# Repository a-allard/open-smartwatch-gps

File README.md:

# Open-Smartwatch KiCAD files

Repo for kicad schematic, board and gerber files. This project is in development and is not ready for release.

If all you want to know is how to build skip down to [Build Info](##Build Info)

#### Forking to move forward

The [original project ](https://github.com/Open-Smartwatch/open-smartwatch-gps) seems to have lost some momentum on development.  There is an [issue here](https://github.com/Open-Smartwatch/open-smartwatch-gps/issues/10) to discuss merging these changes into the original project.  One of the goals of this fork and update is to minimize any serious changes to [the os](https://github.com/Open-Smartwatch/open-smartwatch-os).  If all goes well, the OS should be able to be dropped on here with little to no modifications.  (that is the goal time will tell for sure.)

Right now this is a 2 layer design.  If this works it will greatly reduce the overall cost.  Have to see how this performs.

## Tools

To view/modify the files from this repository install [KiCAD](https://kicad.org).  You'll need version 7.0 or higher.  This will be bumped in Janurary of 2024 to KiCad 8.0.

All footprints, schematic symbols and 3d models should be self contained winthin the project.  This means you should be able to open the kicad project anywhere with or without the default kicad libraries and play with things without worry about missing pieces.

## Schematic
Updated as of 10/20/2023.  May change but if it does it should be minor changes.

Update on 1/7/2024.... Happy New Year to all!  Been quite for awhile as getting boards built and tested took quite a while.  Found a few issues.  Working on fixing them before another spin.  Probably be respinning sometime around May...?

## Plots

## Build Info

To get some raw PCBs the best way would be [pcbway](https://pcbway.com).  Once this project has been built and tested the design will be published on pcbway for anyone to order with a couple clicks.

Next you'll have to either build this yourself or get these fabricated.  If you want to get the boards fabricated pcbway does a decent job.  You'll have to export the position files and put the BOM in pcbway format.

If you choose to solder these youself the smallest components are 0402 and QFNs.  Not the most friendly but can be done with a decent soldering iron.

### BOM

NOTE: **This is a preliminary BOM**  After testing this could change some.

[HTML BOM](https://github.com/a-allard/open-smartwatch-gps/blob/master/bom/OSW_GPS_Rev-4.0.html)  (best to download for a pretty view)

For actual parts you'll need
* [Digi-Key cart](https://www.digikey.com/short/5wz73v93) with most everything needed for a build of 1.
* [Display](https://www.buydisplay.com/1-28-inch-tft-lcd-display-240x240-round-circle-screen-for-smart-watch)
* A LiPo battery (Has not yet been selected but you should be able to power this from USB for initial debugging.  Any generic lipo should work just make sure the pinout works with the connector)

Total cost from DK ~$55.  The display is ~$15 including shipping.  With a battery this should bring the total BOM cost per watch to about ~$110 including boards from pcbway.com.  Note this is for a single watch but you'll have to order 5 boards from pcbway.com

Don't forget to get some decent fine solder while or solder paste as you will need it!

If you like this project, please consider supporting my open source projects through:

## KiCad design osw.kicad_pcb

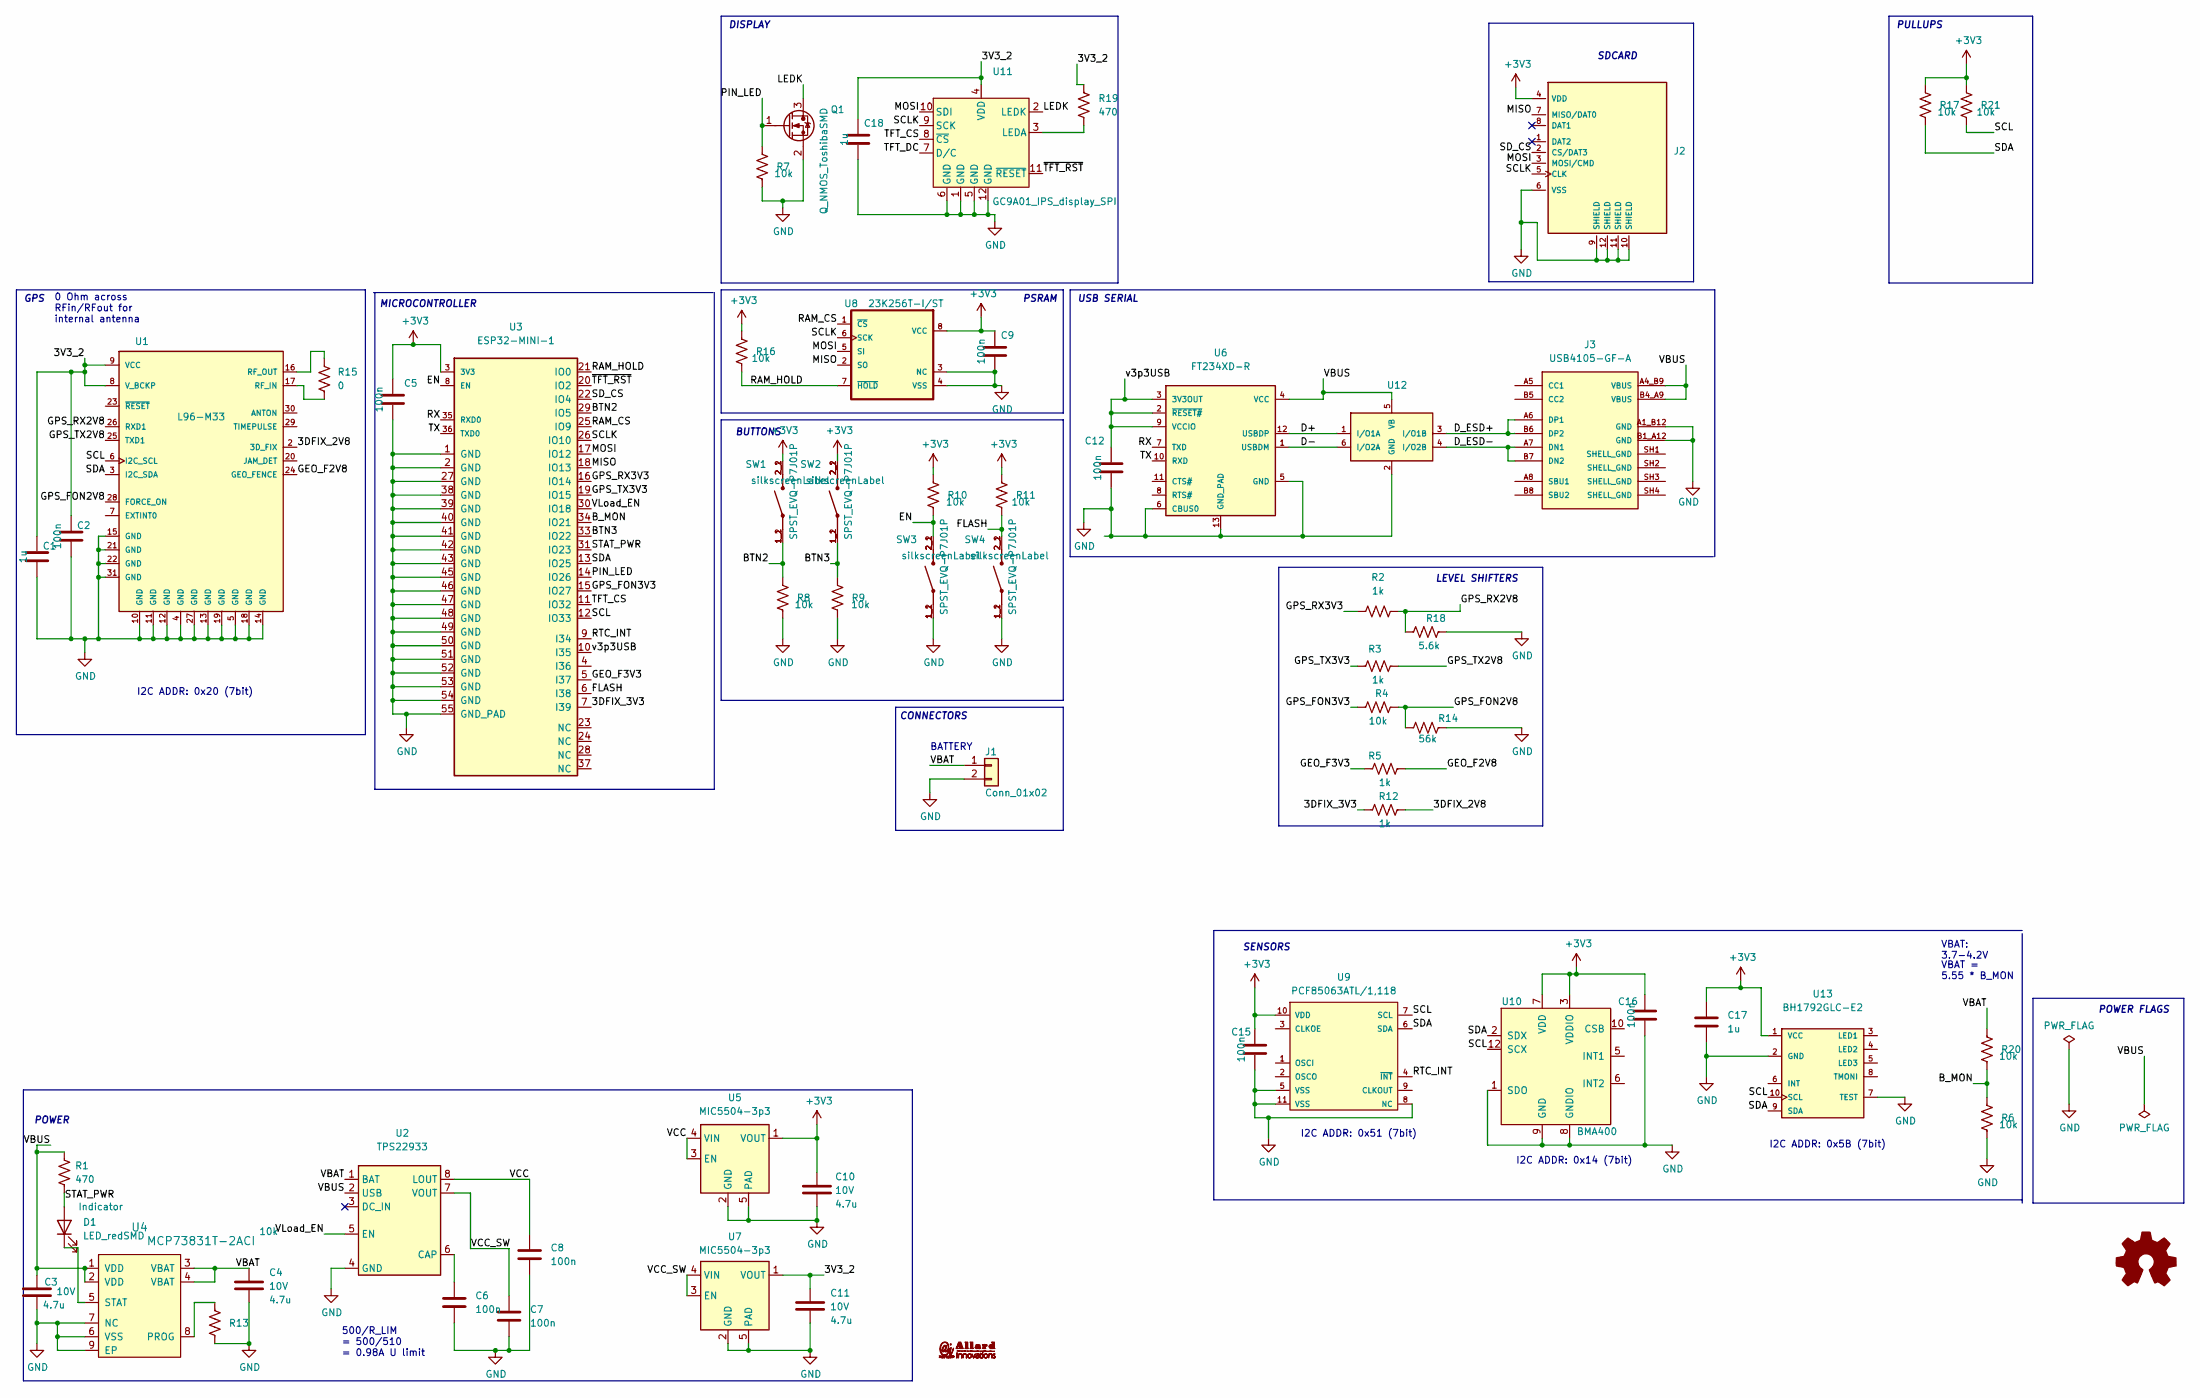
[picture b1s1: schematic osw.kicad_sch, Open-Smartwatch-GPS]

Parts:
C1, C17, C18: 1u; CAPC100X50X60L25N; Voltage 10V; Tolerance 10%; MPN GRM155Z71A105KE01J; DigiKey_PN 490-GRM155Z71A105KE01JCT-ND
C2, C5, C6, C7, C8, C9, C12, C15, C16: 100n; CAPC100X50X55L25N; Voltage 50V; Tolerance 10%; MPN GRM155R71H104KE14J; DigiKey_PN 490-13342-1-ND
C3, C4, C10, C11: cap0402_4p7u10V; C_0402_1005Metric_osw; Voltage 10V; MPN CC0402MRX5R6BB475; DigiKey_PN 311-1734-1-ND
D1: LED_redSMD; Harvatek_LED_osw; MPN B0221USD-02D000154U1930; DigiKey_PN 3147-B0221USD-02D000154U1930CT-ND
G1: LOGO; aiLogo
J1: Conn_01x02; PinHeader_1x02_P2.54mm_Vertical; MPN B2B-EH-A; DigiKey_PN 455-B2B-EH-A-ND
J2: microSD_MEM2067-02-180-00-A_REVB; GCT_MEM2067-02-180-00-A_REVB; MPN MEM2067-02-180-00-A; Mouser_PN 640-MEM20670218000A
J3: USB4105-GF-A; GCT_USB4105-GF-A; MPN USB4105-GF-A
Q1: Q_NMOS_ToshibaSMD; SOT23-3P95_240X105L35X42L; MPN T2N7002AK,LM; DigiKey_PN T2N7002AKLMCT-ND
R1, R19: res0402_470; R_0402_1005Metric_osw; MPN RC0402FR-07470RL; DigiKey_PN 311-470LRCT-ND
R2, R3, R5, R12: 1k; RESC100X50X40L25N; Tolerance 1%; MPN ERJ-2RKF1001X; DigiKey_PN P1.00KLCT-ND
R4, R6, R7, R8, R9, R10, R11, R13, R16, R17, R20, R21: 10k; RESC100X50X40L25N; Tolerance 1%; MPN ERJ-2RKF1002X; DigiKey_PN P10.0KLCT-ND
R14: res0402_56k; R_0402_1005Metric_osw; MPN RC0402JR-0756KL; DigiKey_PN 311-56KJRCT-ND
R15: res0402_0; R_0402_1005Metric_osw; MPN RC0402FR-070RL; DigiKey_PN 311-0.0LRCT-ND
R18: res0402_5p6k; R_0402_1005Metric_osw; MPN RC0402FR-135K6L; DigiKey_PN 13-RC0402FR-135K6LCT-ND
SW1, SW2, SW3, SW4: SPST_EVQ-P7J01P; SW_EVQ-P7J01P; MPN EVQ-P7J01P; Mouser_PN 667-EVQP7J01P
U1: L96-M33; XCVR_L96-M33; Mouser_PN 277-L96-M33; DigiKey_PN 2958-L96-M33CT-ND
U2: TPS22933; uqfn_1p5x1p5_8_tps22933; MPN TPS22933ARSET; DigiKey_PN 296-TPS22933ARSETCT-ND
U3: ESP32-MINI-1; XCVR_ESP32-MINI-1; Mouser_PN 356-ESP32-MINI1PH3Q0; DigiKey_PN 1965-ESP32-MINI-1-N4CT-ND
U4: MCP73831T-2ACI; PSON9P50_200X300X80L40X25T135X125L; MPN MCP73831T-2ACI/MC; DigiKey_PN MCP73831T-2ACI/MCCT-ND
U5, U7: MIC5504-3p3; VREG_MIC5504-3.3YMT-TZ; MPN MIC5504-3.3YMT-TZ; DigiKey_PN 576-4310-1-ND
U6: FT234XD-R; SON45P300X300X80-13N; MPN FT234XD-R; DigiKey_PN 768-1178-1-ND
U8: 23K256T-I/ST; SOP8P65_300X640X120L47X24L; MPN 23K256T-I/ST; DigiKey_PN 23K256T-I/STCT-ND
U9: PCF85063ATL/1,118; 10-DFN(2.6X2.6)_PCF85063A; MPN PCF85063ATL/1,118; DigiKey_PN 568-10235-1-ND
U10: BMA400; LGA-12_2x2mm_P0.5mm; MPN BMA400; DigiKey_PN 828-1081-1-ND
U11: GC9A01_IPS_display_SPI; GC9A01_IPS_display_under
U12: esd_USB_IP4234CZ6; SOT23-6P95_275X110L45X32N; MPN IP4234CZ6,125; DigiKey_PN 1727-4717-1-ND
U13: BH1792GLC-E2; XDCR_BH1792GLC-E2; MPN BH1792GLC-E2; DigiKey_PN BH1792GLC-E2CT-ND

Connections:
+3V3: C5.1, C9.1, C10.1, C15.1, C16.1, C17.1, J2.4 (VDD), R10.1, R11.1, R16.1, R17.1, R21.1, SW1.2_1, SW1.2_2, SW2.2_1, SW2.2_2, U3.3 (3V3), U5.1 (VOUT), U8.8 (VCC), U9.10 (VDD), U10.3 (VDDIO), U10.7 (VDD), U13.1 (VCC)
/3DFIX_2V8: R12.2, U1.2 (3D_FIX)
/3DFIX_3V3: R12.1, U3.7 (I39)
/3V3_2: C1.1, C2.1, C11.1, C18.1, R19.1, U1.8 (V_BCKP), U1.9 (VCC), U7.1 (VOUT), U11.4 (VDD)
/BTN2: R8.1, SW1.1_1, SW1.1_2, U3.29 (IO5)
/BTN3: R9.1, SW2.1_1, SW2.1_2, U3.33 (IO22)
/B_MON: R6.1, R20.2, U3.34 (IO21)
/D+: U6.12 (USBDP), U12.1 (I/O1A)
/D-: U6.1 (USBDM), U12.6 (I/O2A)
/D_ESD+: J3.A6 (DP1), J3.B6 (DP2), U12.3 (I/O1B)
/D_ESD-: J3.A7 (DN1), J3.B7 (DN2), U12.4 (I/O2B)
/EN: R10.2, SW3.2_1, SW3.2_2, U3.8 (EN)
/FLASH: R11.2, SW4.2_1, SW4.2_2, U3.6 (I38)
/GEO_F2V8: R5.2, U1.24 (GEO_FENCE)
/GEO_F3V3: R5.1, U3.5 (I37)
/GPS_FON2V8: R4.2, R14.1, U1.28 (FORCE_ON)
/GPS_FON3V3: R4.1, U3.15 (IO27)
/GPS_RX2V8: R2.2, R18.1, U1.26 (RXD1)
/GPS_RX3V3: R2.1, U3.16 (IO14)
/GPS_TX2V8: R3.2, U1.25 (TXD1)
/GPS_TX3V3: R3.1, U3.19 (IO15)
/LEDK: Q1.3 (D), U11.2 (LEDK)
/MISO: J2.7 (MISO/DAT0), U3.18 (IO13), U8.2 (SO)
/MOSI: J2.3 (MOSI/CMD), U3.17 (IO12), U8.5 (SI), U11.10 (SDI)
/PIN_LED: Q1.1 (G), R7.1, U3.14 (IO26)
/RAM_CS: U3.25 (IO9), U8.1 (~CS)
/RAM_HOLD: R16.2, U3.21 (IO0), U8.7 (~HOLD)
/RTC_INT: U3.9 (I34), U9.4 (~INT)
/RX: U3.35 (RXD0), U6.7 (TXD)
/SCL: R21.2, U1.6 (I2C_SCL), U3.12 (IO33), U9.7 (SCL), U10.12 (SCX), U13.10 (SCL)
/SCLK: J2.5 (CLK), U3.26 (IO10), U8.6 (SCK), U11.9 (SCK)
/SDA: R17.2, U1.3 (I2C_SDA), U3.13 (IO25), U9.6 (SDA), U10.2 (SDX), U13.9 (SDA)
/SD_CS: J2.2 (CS/DAT3), U3.22 (IO4)
/STAT_PWR: D1.2 (A), R1.1, U3.31 (IO23)
/TFT_CS: U3.11 (IO32), U11.8 (~CS)
/TFT_DC: U11.7 (D/C)
/TX: U3.36 (TXD0), U6.10 (RXD)
/VBAT: C4.1, J1.1, R20.1, U2.1 (BAT), U4.3 (VBAT), U4.4 (VBAT)
/VBUS: C3.2, J3.A4_B9 (VBUS), J3.B4_A9 (VBUS), R1.2, U2.2 (USB), U4.1 (VDD), U4.2 (VDD), U6.4 (VCC), U12.5 (VB)
/VCC: C8.1, U2.8 (LOUT), U5.3 (EN), U5.4 (VIN)
/VCC_SW: C7.1, U2.7 (VOUT), U7.3 (EN), U7.4 (VIN)
/VLoad_EN: U2.5 (EN), U3.30 (IO18)
/v3p3USB: C12.1, U3.10 (I35), U6.2 (~RESET#), U6.3 (3V3OUT), U6.9 (VCCIO)
/~TFT_RST: U3.20 (IO2), U11.11 (~RESET)
GND: C1.2, C2.2, C3.1, C4.2, C5.2, C6.2, C7.2, C8.2, C9.2, C10.2, C11.2, C12.2, C15.2, C16.2, C17.2, C18.2, J1.2, J2.6 (VSS), J2.9 (SHIELD), J2.10 (SHIELD), J2.11 (SHIELD), J2.12 (SHIELD), J3.A1_B12 (GND), J3.B1_A12 (GND), Q1.2 (S), R6.2, R7.2, R8.2, R9.2, R13.2, R14.2, R18.2, SW3.1_1, SW3.1_2, SW4.1_1, SW4.1_2, U1.4 (GND), U1.5 (GND), U1.10 (GND), U1.11 (GND), U1.12 (GND), U1.13 (GND), U1.14 (GND), U1.15 (GND), U1.18 (GND), U1.19 (GND), U1.21 (GND), U1.22 (GND), U1.27 (GND), U1.31 (GND), U2.4 (GND), U3.1 (GND), U3.2 (GND), U3.27 (GND), U3.38 (GND), U3.39 (GND), U3.40 (GND), U3.41 (GND), U3.42 (GND), U3.43 (GND), U3.45 (GND), U3.46 (GND), U3.47 (GND), U3.48 (GND), U3.49 (GND), U3.50 (GND), U3.51 (GND), U3.52 (GND), U3.53 (GND), U3.54 (GND), U3.55 (GND_PAD), U4.6 (VSS), U4.7 (NC), U4.9 (EP), U5.2 (GND), U5.5 (PAD), U6.5 (GND), U6.6 (CBUS0), U6.13 (GND_PAD), U7.2 (GND), U7.5 (PAD), U8.3 (NC), U8.4 (VSS), U9.5 (VSS), U9.8 (NC), U9.11 (VSS), U10.1 (SDO), U10.8 (GNDIO), U10.9 (GND), U11.1 (GND), U11.5 (GND), U11.6 (GND), U11.12 (GND), U12.2 (GND), U13.2 (GND), U13.7 (TEST)
unnamed: D1.1 (K), U4.5 (STAT)
unnamed: R15.2, U1.17 (RF_IN)
unnamed: R15.1, U1.16 (RF_OUT)
unnamed: C6.1, U2.6 (CAP)
unnamed: R13.1, U4.8 (PROG)
unnamed: R19.2, U11.3 (LEDA)

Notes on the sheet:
SENSORS
LEVEL SHIFTERS
USB SERIAL
BATTERY
CONNECTORS
I2C ADDR: 0x51 (7bit)
VBAT: 3.7-4.2V
BUTTONS
I2C ADDR: 0x14 (7bit)
POWER
PSRAM
POWER FLAGS
PULLUPS
500/R_LIM = 500/510 = 0.98A U limit
GPS
0 Ohm across RFin/RFout for internal antenna
I2C ADDR: 0x20 (7bit)
MICROCONTROLLER
I2C ADDR: 0x5B (7bit)
DISPLAY
VBAT = 5.55 * B_MON
SDCARD

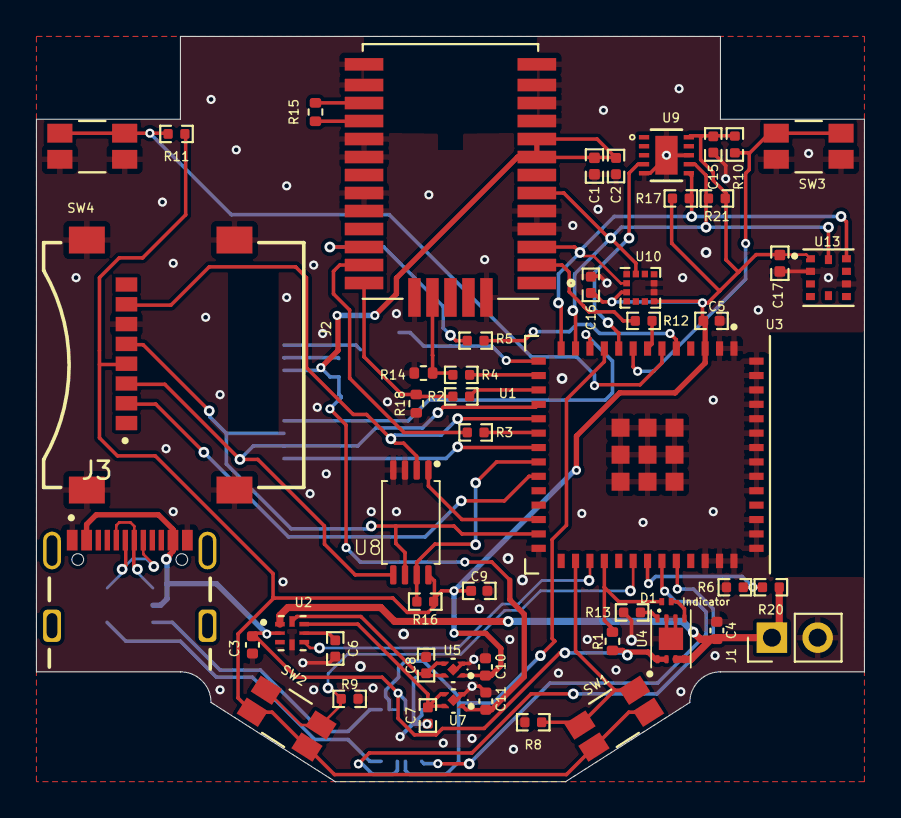
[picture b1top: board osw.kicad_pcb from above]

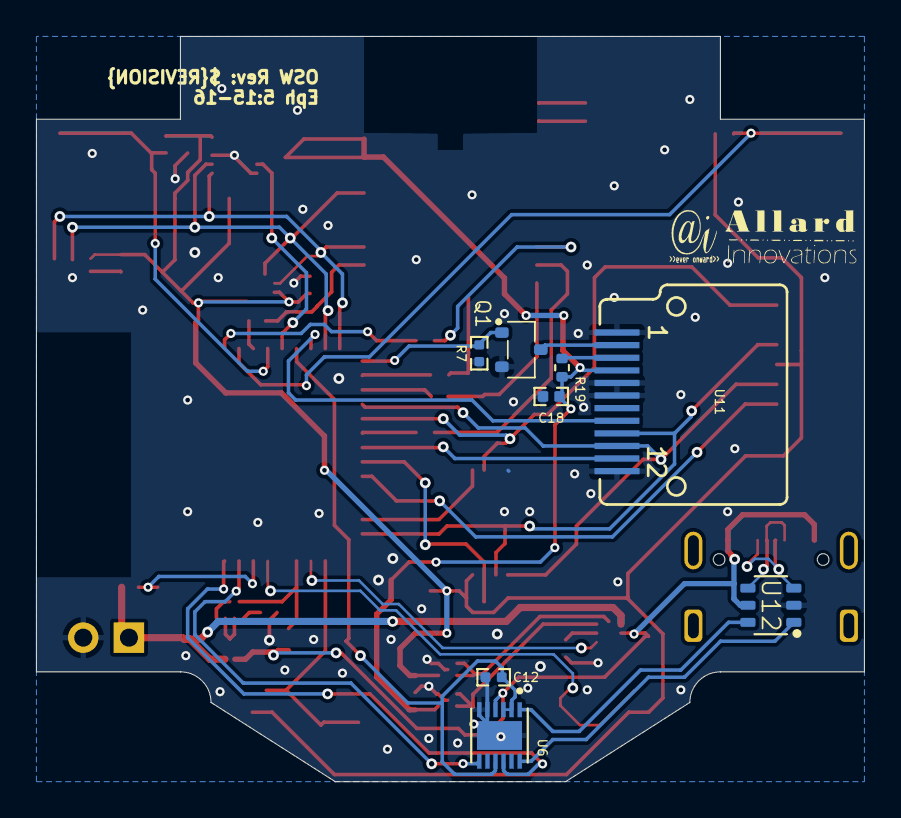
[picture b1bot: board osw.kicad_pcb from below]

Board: 2 copper layers, 46.0 x 41.4 mm, 60 parts (9 on the bottom side), 50 nets.

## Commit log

2022-12-15 Moving this to kicad 6 and looking at potential solutions to adding a buzzer and heart-rate monitor. Have to see if original repo owner is open to this.
2022-12-15 Updating the libs to kicad 6 as well.
2022-12-16 Moving all library items into this repo and adding full manf# info to all parts. Also adding new parts where some are now obsolete.
2022-12-18 Updates to the libs getting new parts for rev 4.
2022-12-19 Continuing to update symbols and models and moving all symbols to metric grids.
2022-12-19 Finished updating symbols.
2022-12-20 Updates to the libs to get more footprints and symbols added to this project.
2022-12-20 another step model for the model.
2022-12-20 Updates to the board and schematic.
2022-12-21 Adding a very small regulater for running everything.
2022-12-27 Updates to the libs and the schematic. Only need to update the battery charger a FET and a couple of resisters. After that this should be good to go to layout.
2022-12-27 A couple of new footprints in the lib.
2022-12-27 Update readme.
2022-12-27 Updating the display connector footprint.
2022-12-31 Getting close to schemtatic done. Still have RAM to figure out and need to finish backlight driver FET. Otherwise schematiclly things are looking good.
2023-01-01 Finished schematic. Ready to begin board layout.
2023-01-01 Updating the docs for the schematic. May need to swap out the ESP chip as it is quite wide for the board layout....
2023-01-07 Updates to the schematic to use a smaller packaged ESP32.
2023-10-19 Getting back to this now that someone from the OSW community has mentioned this would be good.
2023-10-20 Working through some junk in the schematic. Got the board outline done and components all on the board. Very rough layout done. More work needed before traces start getting drawn.
2023-10-20 Forgot to save board before last commit.
2023-10-21 Had to redo the schematic libs as goofball chose a bad grid size. Not a big deal.... But this will make any changes easier. Be ware if you update all symbols some will breakgit status!
2023-10-21 Updates as the schematic is getting close to done.
2023-10-21 Updated dates.
2023-10-21 Starting on the layout in ernest now.
2023-10-21 Adding more docs on the ESP32. If this works out well the ESP will get repined for layout sake.
2023-10-21 Updated ESP mod in schematic with better symbol.:
2023-10-21 Updates to schematic and board.
2023-10-21 Added some more track sizes.
2023-10-21 Adding another kicad file.
2023-10-21 working on the layout.
2023-10-22 Added some dimensions to the layout and corrected all the edge cuts so the board is symetric.
2023-10-22 Repinned out the ESP32 to get a bit better layout.
2023-10-22 Updates to several footprints as they were not quite correct. Finished layout. All done on a simple two layer board. Need to look over the design once more before ordering prototypes.
2023-10-22 Updating the schematic docs.
2023-10-22 Adding HTML BOM
2023-10-23 Optimizing the layout a bit.
2023-10-23 Adding some silkscreen dressup.
2023-10-24 Footprint looked a bit small... After looking at the datasheet turns out it was very too small. SHould be good now.
2023-10-24 Finishing up the board. Provided nothing jumps out looking through the DOCs later this should be good to order
2023-10-24 Updating the BOM with a good JST connector that should work for most LiPo batteries."
2023-10-24 Adding the BOM ini file so Allard doesn't have to remember to keep changing the settings.
2023-10-24 JST connector properties added to board layout for html bom generator.
2023-10-28 Updates for final fab
2023-10-29 Updating the repo with the actual fab files.
2023-10-29 Removing the older rev gerbers. All fab stuff is now in fab folder.
2023-10-29 Adding some updates to the gitignore and movingh the bom to the fab folder.
2023-10-29 Updating readme.
2023-10-29 Adding plots of board.
2023-10-29 readme formatting.
2023-10-29 Adding pos files.
2023-10-29 Updated readme to reflect how to order.
2023-10-31 Adding another dimension to the layout for modeling the case.
2023-11-05 Adding a cad model for a basic case. Not sure it'll work
2024-01-07 Corrected a library FP. Also corrected the fact the regulators need to be pulled up to work correctly. Rotated LCD FP so it folds correctly now. Only thing left is to find the nasty short that is cau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
2024-01-07 Update README.md
    Updating with current status.
2024-01-07 Fixing the ESD diode array that was mis-pinned.
2024-01-08 Adding a few comments about what to use in the next gen.
2024-01-08 Removing some obsolete stuff and getting thigns better updated. Also should use smaller FPs in new design as smaller parts exist.
2024-01-09 Updates to a bunch of symbols and the entire schematic now matches the libs.... Now onto fixing the short.
2024-01-09 Updating some FPs.
2024-01-10 Updates.
2024-01-10 Moving things to kicad 8.
2024-01-10 Updating the FP for a SOT23.
2024-01-12 Got USB connector chagned.
2024-01-14 Updating the layout to send to PCBway again....
